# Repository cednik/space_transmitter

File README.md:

# space_transmitter
Big flashing thing for final part of summer camp game

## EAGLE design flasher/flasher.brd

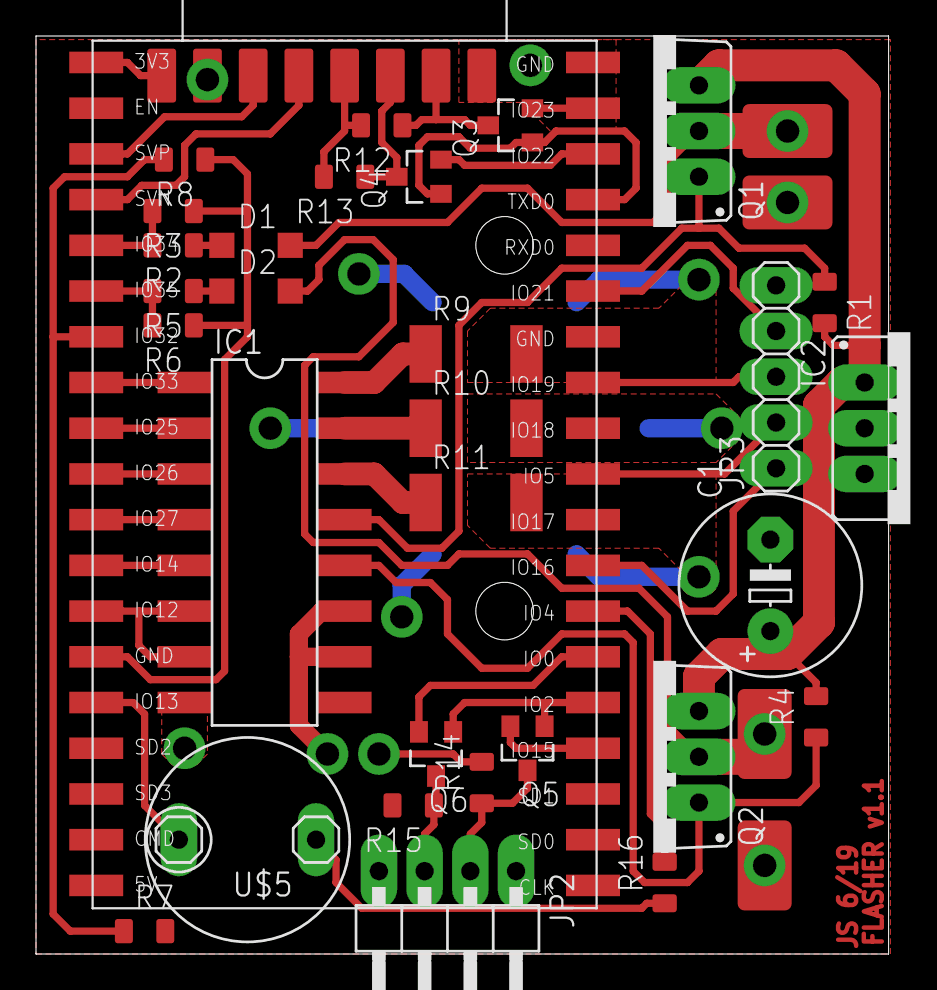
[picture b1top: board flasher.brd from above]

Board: 2 copper layers, 47.4 x 51.0 mm, 38 parts (1 on the bottom side), 45 nets.

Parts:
C1: E5-10,5
D1, D2: SOD123
IC1: ULN2004A_BIG_SMD; DIL16_BIG_SMD
IC2: 78XXS
IM1: DEVKITC_BIG_SMD
JP1, JP4: PINH2X04SMD
JP2: 1X04/90
JP3: 1X05
LED1: HEX_HEATSINK
Q1, Q2: IRF4905; TO220BV
Q3, Q4, Q5, Q6: SOT23_DIST
R1, R4: 33k; R0805S
R2, R5: 5k6; R0805S
R3, R6: 3k3; R0805S
R7, R12, R13, R14, R15: 4k7; R0805S
R8: 1k; R0805S
R9, R10, R11: 10R; R2512
R16: 0R; R0805S
U$1, U$2, U$3, U$4: PAD_1SIDE_LARGE; 3X5MM
U$5: PIEZO

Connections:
!B: IC1.16, R9.1
!G: IC1.15, R10.1
!PWR1_EN: IC1.13, Q1.G, R1.1
!PWR2_EN: IC1.12, Q2.G, R4.1
!R: IC1.14, R11.1
!W: IC1.10, IC1.11
+3V3: IM1.1, JP4.T1
+5V: IC1.9, IC2.OUT, IM1.19, JP1.T1, JP2.4, LED1.B+, LED1.G+, LED1.R+, R7.2, R12.2, R13.2, R14.2, R15.2
B: IC1.1, IM1.8
BA: LED1.B-, R9.2
BUZZ-N: R16.1, U$5.-
BUZZ_N: IM1.26, R16.2
BUZZ_P: IM1.15, U$5.+
G: IC1.2, IM1.9
GA: LED1.G-, R10.2
GND: C1.-, IC1.8, IC2.GND, IM1.14, IM1.32, IM1.38, JP1.B1, JP1.B2, JP1.B3, JP1.B4, JP1.T4, JP2.1, JP3.5, JP4.B1, JP4.B2, JP4.B3, JP4.B4, JP4.T2, R3.1, R6.1, R8.1, U$2.1, U$4.1
IO0: IM1.25, Q6.2
IO0_5: JP2.3, Q6.3, R15.1
IO1_EN: IM1.24, Q5.1, Q6.1
IO2_EN: IM1.35, Q3.1, Q4.1
IO5: IM1.29, JP3.2
IO15: IM1.23, Q5.2
IO15_5: JP2.2, Q5.3, R14.1
IO16: IM1.27, JP3.1
IO19: IM1.31, JP3.3
IO21: IM1.33, JP3.4
IO22: IM1.36, Q4.2
IO22_5: JP1.T2, Q4.3, R13.1
IO23: IM1.37, Q3.2
IO23_5: JP1.T3, Q3.3, R12.1
IO36: IM1.3, JP4.T3
IO39: IM1.4, JP4.T4
PWR1: D1.A, Q1.D, U$1.1
PWR1+: D1.C, R2.1
PWR1_EN: IC1.4, IM1.11
PWR1_MEAS: IM1.5, R2.2, R3.2
PWR2: D2.A, Q2.D, U$3.1
PWR2+: D2.C, R5.1
PWR2_EN: IC1.5, IM1.12
PWR2_MEAS: IM1.6, R5.2, R6.2
PWR_MEAS: IM1.7, R7.1, R8.2
R: IC1.3, IM1.10
RA: LED1.R-, R11.2
VCC: C1.+, IC2.IN, Q1.S, Q2.S, R1.2, R4.2
W: IC1.6, IC1.7, IM1.13

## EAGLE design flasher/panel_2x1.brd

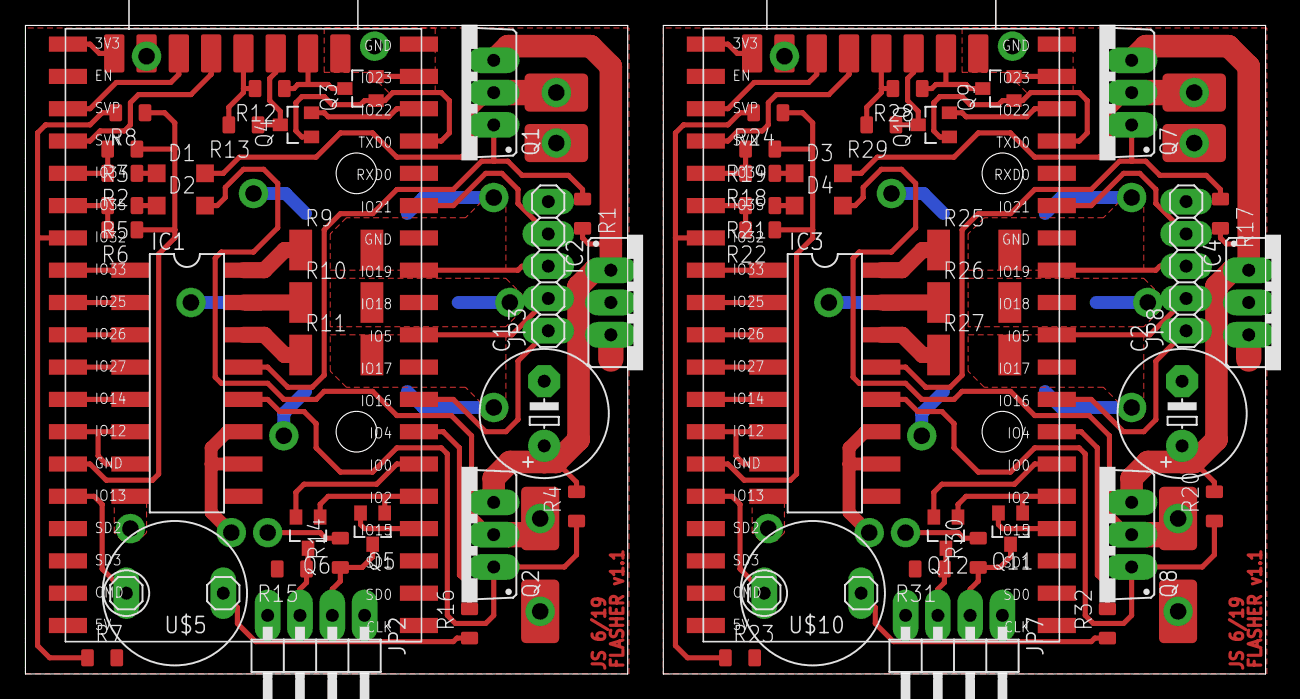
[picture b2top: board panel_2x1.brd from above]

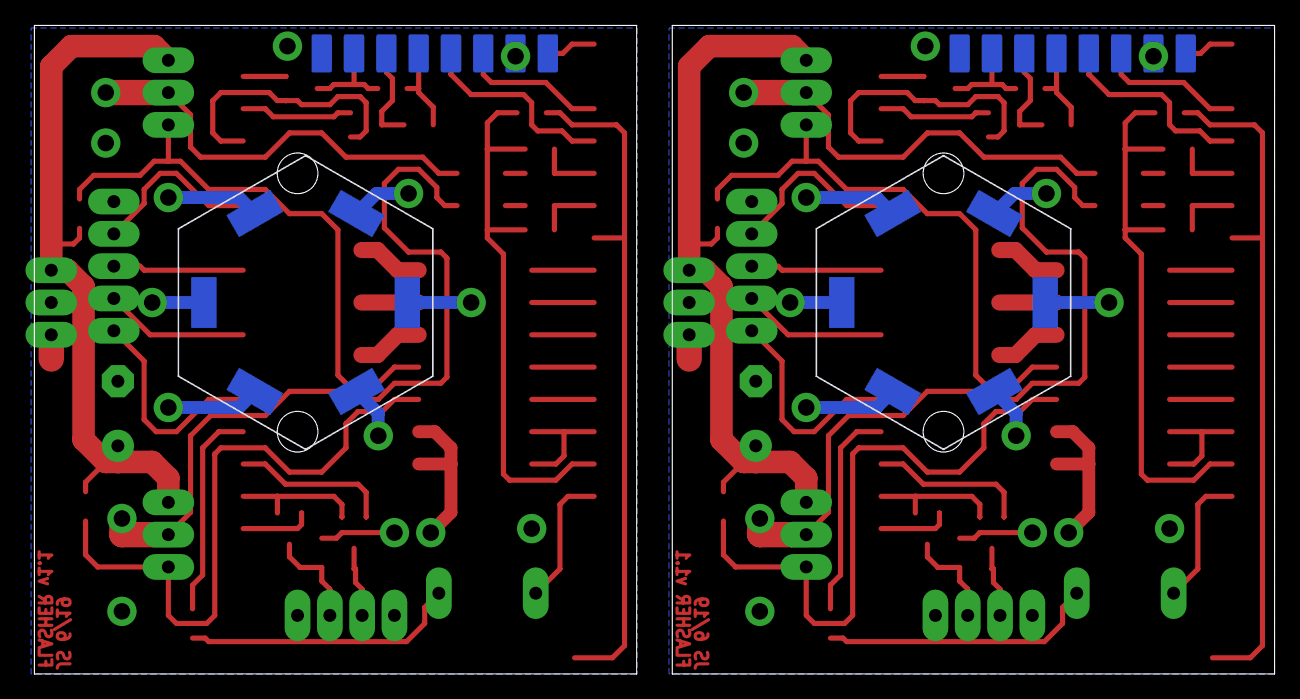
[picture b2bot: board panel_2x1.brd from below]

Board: 2 copper layers, 97.5 x 51.0 mm, 76 parts (2 on the bottom side), 90 nets.

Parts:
C1, C2: E5-10,5
D1, D2, D3, D4: SOD123
IC1, IC3: ULN2004A_BIG_SMD; DIL16_BIG_SMD
IC2, IC4: 78XXS
IM1, IM2: DEVKITC_BIG_SMD
JP1, JP4, JP5, JP6: PINH2X04SMD
JP2, JP7: 1X04/90
JP3, JP8: 1X05
LED1, LED2: HEX_HEATSINK
Q1, Q2, Q7, Q8: IRF4905; TO220BV
Q3, Q4, Q5, Q6, Q9, Q10, Q11, Q12: SOT23_DIST
R1, R4, R17, R20: 100k; R0805S
R2, R5, R12, R13, R14, R15, R16, R18, R21, R28, R29, R30, R31, R32: 18k; R0805S
R3, R6, R19, R22: 33k; R0805S
R7, R23: 4k7; R0805S
R8, R24: 1k; R0805S
R9, R10, R11, R25, R26, R27: 10R; R2512
U$1, U$2, U$3, U$4, U$6, U$7, U$8, U$9: PAD_1SIDE_LARGE; 3X5MM
U$5, U$10: PIEZO

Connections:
!B: IC1.16, R9.1
!B1: IC3.16, R25.1
!G: IC1.15, R10.1
!G1: IC3.15, R26.1
!PWR1_EN: IC1.13, Q1.G, R1.1
!PWR1_EN1: IC3.13, Q7.G, R17.1
!PWR2_EN: IC1.12, Q2.G, R4.1
!PWR2_EN1: IC3.12, Q8.G, R20.1
!R: IC1.14, R11.1
!R1: IC3.14, R27.1
!W: IC1.10, IC1.11
!W1: IC3.10, IC3.11
+3V1: IM2.1, JP6.T1
+3V3: IM1.1, JP4.T1
+5V: IC1.9, IC2.OUT, IM1.19, JP1.T1, JP2.4, LED1.B+, LED1.G+, LED1.R+, R7.2, R12.2, R13.2, R14.2, R15.2
+5V1: IC3.9, IC4.OUT, IM2.19, JP5.T1, JP7.4, LED2.B+, LED2.G+, LED2.R+, R23.2, R28.2, R29.2, R30.2, R31.2
B: IC1.1, IM1.8
B1: IC3.1, IM2.8
BA: LED1.B-, R9.2
BA1: LED2.B-, R25.2
BUZZ-N: R16.1, U$5.-
BUZZ-N1: R32.1, U$10.-
BUZZ_N: IM1.26, R16.2
BUZZ_N1: IM2.26, R32.2
BUZZ_P: IM1.15, U$5.+
BUZZ_P1: IM2.15, U$10.+
G: IC1.2, IM1.9
G1: IC3.2, IM2.9
GA: LED1.G-, R10.2
GA1: LED2.G-, R26.2
GND: C1.-, IC1.8, IC2.GND, IM1.14, IM1.32, IM1.38, JP1.B1, JP1.B2, JP1.B3, JP1.B4, JP1.T4, JP2.1, JP3.5, JP4.B1, JP4.B2, JP4.B3, JP4.B4, JP4.T2, R3.1, R6.1, R8.1, U$2.1, U$4.1
GND1: C2.-, IC3.8, IC4.GND, IM2.14, IM2.32, IM2.38, JP5.B1, JP5.B2, JP5.B3, JP5.B4, JP5.T4, JP6.B1, JP6.B2, JP6.B3, JP6.B4, JP6.T2, JP7.1, JP8.5, R19.1, R22.1, R24.1, U$7.1, U$9.1
IO0: IM1.25, Q6.2
IO0_1: JP7.3, Q12.3, R31.1
IO0_5: JP2.3, Q6.3, R15.1
IO1_EN: IM1.24, Q5.1, Q6.1
IO1_EN1: IM2.24, Q11.1, Q12.1
IO2_EN: IM1.35, Q3.1, Q4.1
IO2_EN1: IM2.35, Q9.1, Q10.1
IO5: IM1.29, JP3.2
IO15: IM1.23, Q5.2
IO15_1: JP7.2, Q11.3, R30.1
IO15_5: JP2.2, Q5.3, R14.1
IO16: IM1.27, JP3.1
IO19: IM1.31, JP3.3
IO20: IM2.37, Q9.2
IO21: IM1.33, JP3.4
IO22: IM1.36, Q4.2
IO22_1: JP5.T2, Q10.3, R29.1
IO22_5: JP1.T2, Q4.3, R13.1
IO23: IM1.37, Q3.2
IO23_1: JP5.T3, Q9.3, R28.1
IO23_5: JP1.T3, Q3.3, R12.1
IO24: IM2.36, Q10.2
IO25: IM2.25, Q12.2
IO26: IM2.23, Q11.2
IO27: IM2.33, JP8.4
IO28: IM2.31, JP8.3
IO31: IM2.29, JP8.2
IO32: IM2.27, JP8.1
IO33: IM2.3, JP6.T3
IO34: IM2.4, JP6.T4
IO36: IM1.3, JP4.T3
IO39: IM1.4, JP4.T4
PWR1: D1.A, Q1.D, U$1.1
PWR1+: D1.C, R2.1
PWR1+1: D3.C, R18.1
PWR1_EN: IC1.4, IM1.11
PWR1_EN1: IC3.4, IM2.11
PWR1_MEAS: IM1.5, R2.2, R3.2
PWR1_MEAS1: IM2.5, R18.2, R19.2
PWR2: D2.A, Q2.D, U$3.1
PWR2+: D2.C, R5.1
PWR2+1: D4.C, R21.1
PWR2_EN: IC1.5, IM1.12
PWR2_EN1: IC3.5, IM2.12
PWR2_MEAS: IM1.6, R5.2, R6.2
PWR2_MEAS1: IM2.6, R21.2, R22.2
PWR3: D3.A, Q7.D, U$6.1
PWR4: D4.A, Q8.D, U$8.1
PWR_MEAS: IM1.7, R7.1, R8.2
PWR_MEAS1: IM2.7, R23.1, R24.2
R: IC1.3, IM1.10
R1: IC3.3, IM2.10
RA: LED1.R-, R11.2
RA1: LED2.R-, R27.2
VCC: C1.+, IC2.IN, Q1.S, Q2.S, R1.2, R4.2
VCC1: C2.+, IC4.IN, Q7.S, Q8.S, R17.2, R20.2
W: IC1.6, IC1.7, IM1.13
W1: IC3.6, IC3.7, IM2.13

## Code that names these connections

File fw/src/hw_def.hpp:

#pragma once

#include <display.hpp>
#include <PS2Keyboard.h>
#include <SmartLeds.h>
#include "button.hpp"

#include <unordered_map>
#include <string>

const uint8_t PIN_GEN_P           = 36;
const uint8_t PIN_GEN_N           = 39;

const gpio_num_t PIN_GEN_SHORT    = GPIO_NUM_21;

const gpio_num_t PIN_BTN          = GPIO_NUM_17;

const gpio_num_t I2C_SDA          = GPIO_NUM_0;
const gpio_num_t I2C_SCL          = GPIO_NUM_15;

const gpio_num_t PS2_DATA         = GPIO_NUM_23;
const gpio_num_t PS2_CLK          = GPIO_NUM_22;

const gpio_num_t PWR_MEAS         = GPIO_NUM_32;

const gpio_num_t PWR1_MEAS        = GPIO_NUM_34;
const gpio_num_t PWR2_MEAS        = GPIO_NUM_35;

const gpio_num_t PWR1_EN          = GPIO_NUM_27;
const gpio_num_t PWR2_EN          = GPIO_NUM_14;
const gpio_num_t PWR3_EN          = GPIO_NUM_5;
const gpio_num_t PWR4_EN          = GPIO_NUM_16;

const gpio_num_t PWR_EN          = GPIO_NUM_12;

const gpio_num_t IO1_EN           = GPIO_NUM_2;
const gpio_num_t IO2_EN           = GPIO_NUM_1;
const gpio_num_t IO_ILED_EN       = GPIO_NUM_18;
const gpio_num_t PIN_ILED         = GPIO_NUM_19;

const gpio_num_t PIN_RED          = GPIO_NUM_26;
const gpio_num_t PIN_GREEN        = GPIO_NUM_25;
const gpio_num_t PIN_BLUE         = GPIO_NUM_33;

const gpio_num_t PIN_BUZZER_P     = GPIO_NUM_13;
const gpio_num_t PIN_BUZZER_N     = GPIO_NUM_4;

const gpio_num_t TXD              = GPIO_NUM_1;
const gpio_num_t RXD              = GPIO_NUM_3;

const double PWM_FREQ = 20000; // Hz
const uint8_t PWM_RESOLUTION = 8; // bits

// PWM channel
enum LED_CHANNEL {
    RED    = 0,
    GREEN  = 1,
    BLUE   = 2,
    BUZZER = 3,
    GEN_SHORT = 4
};

const int LED_COUNT = 1 + 4*60;
const int LED_CHANNEL = 0;

namespace detail {

typedef I2C_master I2C_internal;
I2C_internal i2c_internal ( I2C_NUM_0, I2C_SDA, I2C_SCL );

namespace display {

typedef PCF8574_t<I2C_internal> Display_port;

const int DISPLAY_WIDTH  = 20;
const int DISPLAY_HEIGHT =  4;
const int DISPLAY_PIN_E          = 2;
const int DISPLAY_PIN_RW         = 1;
const int DISPLAY_PIN_RS         = 0;
const int DISPLAY_PIN_DATA       = 4;
const int DISPLAY_PIN_BACKGLIGHT = 3;
const Display_port::address_type DISPLAY_ADDRESS = 0x3F;

Display_port display_port ( i2c_internal, DISPLAY_ADDRESS );

} // namespace display

pin_t pin_btn(PIN_BTN);

} // namespace detail

typedef Display_t <
    detail::display::DISPLAY_WIDTH,
    detail::display::DISPLAY_HEIGHT,
    detail::display::DISPLAY_PIN_E,
    detail::display::DISPLAY_PIN_RW,
    detail::display::DISPLAY_PIN_RS,
    detail::display::DISPLAY_PIN_DATA,
    detail::display::DISPLAY_PIN_BACKGLIGHT > Display;
Display display ( detail::display::display_port );

PS2Keyboard keyboard;

button_t button(detail::pin_btn);

typedef std::unordered_map<std::string, uint8_t> LED_MAP_t;
const LED_MAP_t LED( {
    { "r", RED    },
    { "g", GREEN  },
    { "b", BLUE   },
    { "a", BUZZER }
} );

SmartLed leds( LED_WS2812B, LED_COUNT, PIN_ILED, LED_CHANNEL, SingleBuffer );

void init_hw(void) {
    pinMode(PWR_EN, OUTPUT);

    pinMode(PWR1_EN, OUTPUT);
    pinMode(PWR2_EN, OUTPUT);
    pinMode(PWR3_EN, OUTPUT);
    pinMode(PWR4_EN, OUTPUT);

    pinMode(PIN_GEN_P , ANALOG);
    pinMode(PIN_GEN_N , ANALOG);
    pinMode(PWR_MEAS , ANALOG);
    pinMode(PWR1_MEAS, ANALOG);
    pinMode(PWR2_MEAS, ANALOG);

    pinMode(IO1_EN, OUTPUT);
    digitalWrite(IO1_EN, HIGH);

    pinMode(IO_ILED_EN, OUTPUT);
    digitalWrite(IO_ILED_EN, HIGH);
    
    ledcSetup(RED       , PWM_FREQ, PWM_RESOLUTION);
    ledcSetup(GREEN     , PWM_FREQ, PWM_RESOLUTION);
    ledcSetup(BLUE      , PWM_FREQ, PWM_RESOLUTION);
    ledcSetup(GEN_SHORT , PWM_FREQ, PWM_RESOLUTION);
    
    ledcAttachPin(PIN_RED, RED);
    ledcAttachPin(PIN_GREEN, GREEN);
    ledcAttachPin(PIN_BLUE, BLUE);
    ledcAttachPin(PIN_GEN_SHORT, GEN_SHORT);
    
    pinMode(PIN_BUZZER_N, OUTPUT);
    pinMode(PIN_BUZZER_P, OUTPUT);
    digitalWrite(PIN_BUZZER_N, HIGH);
    digitalWrite(PIN_BUZZER_P, HIGH);

    pinMode(PIN_BTN, INPUT);
    
    detail::i2c_internal.init();
    display.init();
    keyboard.begin(PS2_DATA, PS2_CLK);

}

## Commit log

2019-06-29 Flasher HW
2019-06-29 Remove old box outline
2019-06-30 Change resistors value
2019-06-30 Flasher v1.2: add reverse protection diode and capacitors to stabilizer, add some missing parts value, minor cosmetics changes
2019-06-30 Add FW for basic HW test
2019-07-05 Controller display test
2019-07-05 Separate controller and flasher code
2019-07-05 Keyboard test
2019-07-05 Iled test
2019-07-06 Switch off Iled at startup
2019-07-06 Input line test
2019-07-07 TerminalScreen display template type rename
2019-07-07 Add TerminalScreen::onEnter
2019-07-07 Add generator measurement and charging
2019-07-07 Add on/off commands
2019-07-08 Add wifi ap
2019-07-08 Make server global
2019-07-08 Add shutdown command
2019-07-09 Add multiUpload
2019-07-09 First communication
2019-07-09 Add led timeout
2019-07-10 UDP sync test
2019-07-10 Version zero
2021-08-19 Time machine from Jistojistě
2021-08-19 Balloons blower from Robotický tábor 2021

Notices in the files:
parts and their libraries:
esp32: Creative Commons Attribution-ShareAlike 4.0 International
